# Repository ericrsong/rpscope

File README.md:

This is a clone from jgpeiro's design: https://hackaday.io/project/188051-rpscope/details

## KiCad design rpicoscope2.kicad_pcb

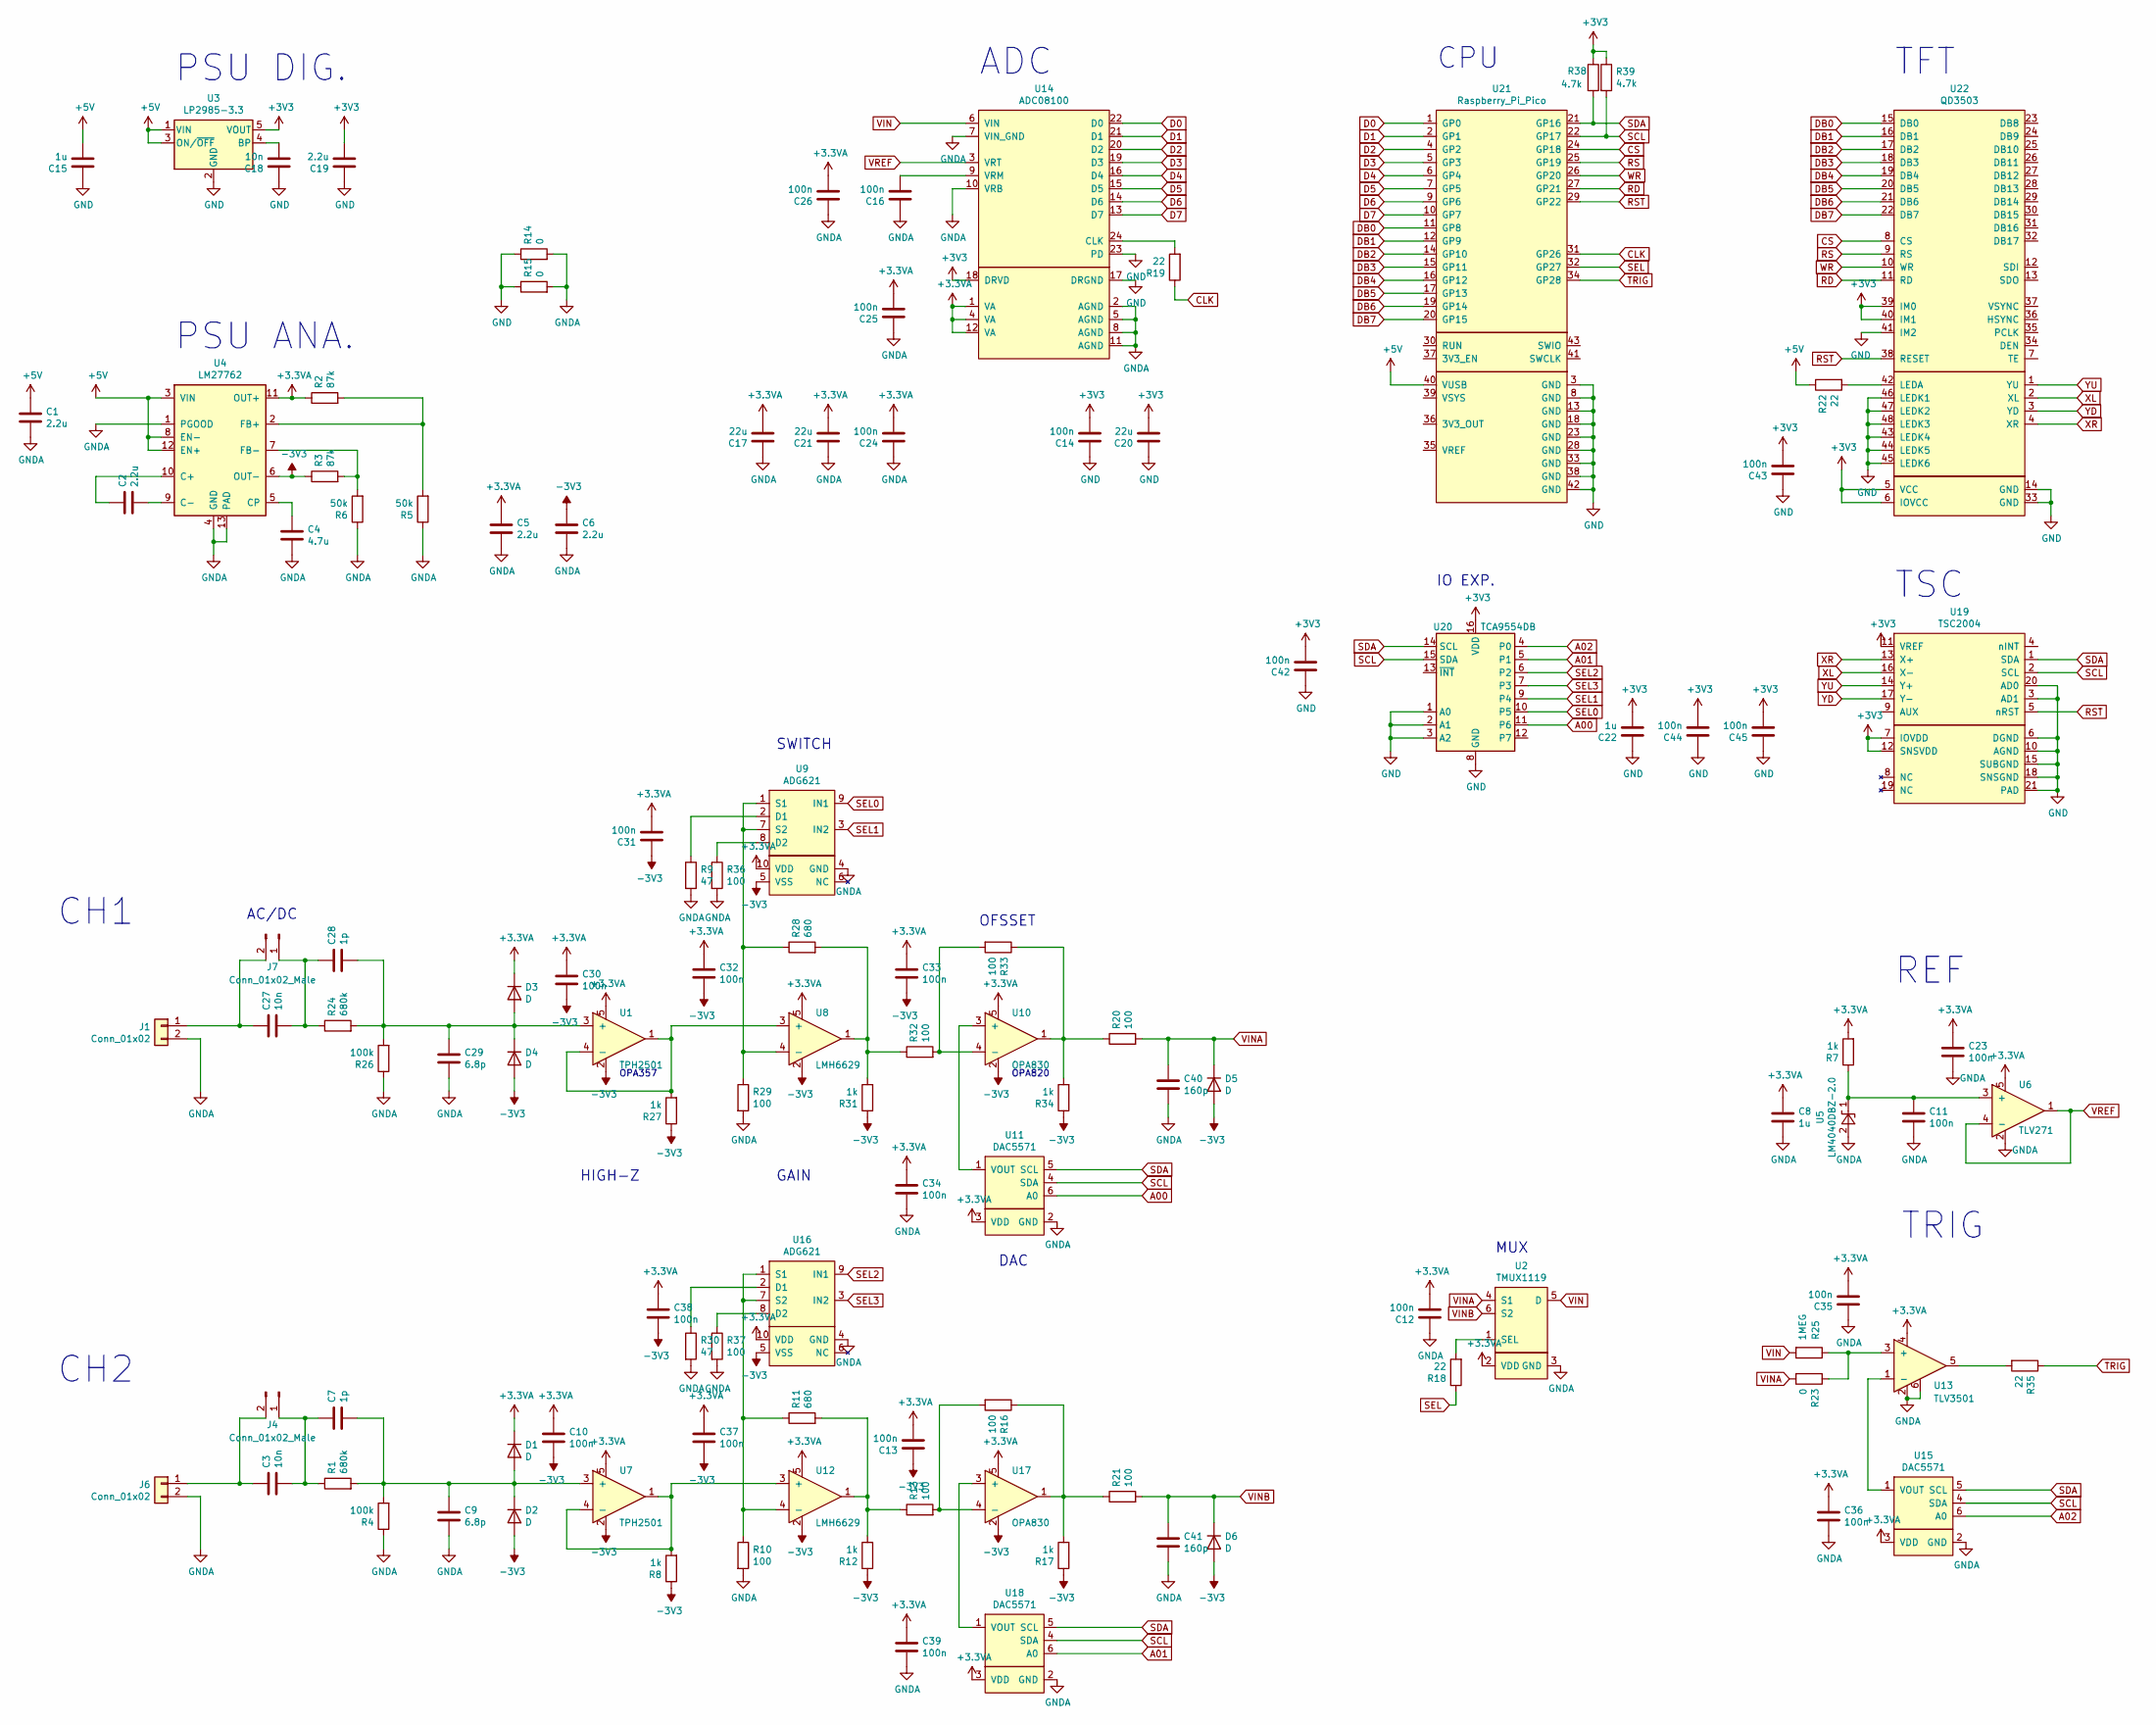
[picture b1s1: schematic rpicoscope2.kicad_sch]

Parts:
C1, C2, C5, C6, C19: 2.2u; C_0603_1608Metric; MFR. Part # CL10A225KO8NNNC; LCSC Part # C23630
C3, C18, C27: 10n; C_0603_1608Metric; MFR. Part # 0603B103K500NT; LCSC Part # C57112
C4: 4.7u; C_0603_1608Metric; MFR. Part # CL10A475KO8NNNC; LCSC Part # C19666
C7, C28: 1p; C_0603_1608Metric; MFR. Part # CL10C010CB8NNNC; LCSC Part # C23969
C8, C15, C22: 1u; C_0603_1608Metric; MFR. Part # CL10A105KB8NNNC; LCSC Part # C15849
C9, C29: 6.8p; C_0603_1608Metric; MFR. Part # 0603CG6R8C500NT; LCSC Part # C1679
C10, C11, C12, C13, C14, C16, C23, C24, C25, C26, C30, C31, C32, C33, C34, C35, C36, C37, C38, C39, C42, C43, C44, C45: 100n; C_0603_1608Metric; MFR. Part # CC0603KRX7R9BB104; LCSC Part # C14663
C17, C20, C21: 22u; C_0603_1608Metric; MFR. Part # CL10A226MQ8NRNC; LCSC Part # C59461
C40, C41: 160p; C_0603_1608Metric; MFR. Part # FN18X104K160PSG; LCSC Part # C235729
D1, D2, D3, D4, D5, D6: D; D_0603_1608Metric
J1, J6: Conn_01x02; SMA_Samtec_SMA-J-P-X-ST-EM1_EdgeMount
J4, J7: Conn_01x02_Male; PinHeader_1x02_P1.00mm_Vertical_SMD_Pin1Left
R1, R24: 680k; R_0603_1608Metric; MFR. Part # 0603WAF6803T5E; LCSC Part # C25822
R2, R3: 87k; R_0603_1608Metric; MFR. Part # 0603WAF8202T5E; LCSC Part # C23254
R4, R26: 100k; R_0603_1608Metric; MFR. Part # 0603WAF1003T5E; LCSC Part # C25803
R5, R6: 50k; R_0603_1608Metric; MFR. Part # 0603WAF1503T5E; LCSC Part # C22807
R7, R8, R12, R17, R27, R31, R34: 1k; R_0603_1608Metric; MFR. Part # 0603WAF1001T5E; LCSC Part # C21190
R9, R30: 47; R_0603_1608Metric; MFR. Part # 0603WAF470JT5E; LCSC Part # C23182
R10, R13, R16, R20, R21, R29, R32, R33, R36, R37: 100; R_0603_1608Metric; MFR. Part # 0603WAF1000T5E; LCSC Part # C22775
R11, R28: 680; R_0603_1608Metric; MFR. Part # 0603WAF6801T5E; LCSC Part # C23212
R14, R15, R23: 0; R_0603_1608Metric; MFR. Part # 0603WAF0000T5E; LCSC Part # C21189
R18, R19, R22, R35: 22; R_0603_1608Metric; MFR. Part # 0603WAF220JT5E; LCSC Part # C23345
R25: 1MEG; R_0603_1608Metric; MFR. Part # 0603WAF220JT5E; LCSC Part # C23345
R38, R39: 4.7k; R_0603_1608Metric; MFR. Part # 0603WAF4701T5E; LCSC Part # C23162
U1, U7: TPH2501; SOT-23-5; LCSC Part # C139385
U2: TMUX1119; SOT-23-6
U3: LP2985-3.3; SOT-23-5; MFR. Part # LP2985-33DBVR; LCSC Part # C95414
U4: LM27762; WSON-12-1EP_3x2mm_P0.5mm_EP1x2.65_ThermalVias; MFR. Part # LM27762DSSR; LCSC Part # C473398
U5: LM4040DBZ-2.0; SOT-23; MFR. Part # LM4040A20IDBZR; LCSC Part # C127070
U6: TLV271; SOT-23-5; LCSC Part # C181500
U8, U12: LMH6629; SOT-23-5; LCSC Part # C206003
U9, U16: ADG621; MSOP-10_3x3mm_P0.5mm; LCSC Part # C208597
U10, U17: OPA830; SOT-23-5; LCSC Part # C181539
U11, U15, U18: DAC5571; SOT-23-6; LCSC Part # C24061
U13: TLV3501; SOT-23-6; LCSC Part # C193413
U14: ADC08100; TSSOP-24_4.4x7.8mm_P0.65mm; LCSC Part # C701581
U19: TSC2004; QFN-20-1EP_4x4mm_P0.5mm_EP2.7x2.7mm; LCSC Part # C128424
U20: TCA9554DB; SSOP-16_5.3x6.2mm_P0.65mm; LCSC Part # C477924
U21: Raspberry_Pi_Pico; RPi_Pico_SMD_TH
U22: QD3503

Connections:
+3.3VA: C5.1, C8.1, C10.1, C12.2, C13.2, C17.2, C21.2, C23.1, C24.2, C25.2, C26.2, C30.1, C31.2, C32.1, C33.1, C34.1, C35.2, C36.1, C37.1, C38.1, C39.1, D1.1 (K), D3.1 (K), R2.1, R7.2, U1.5, U2.2 (VDD), U4.11 (OUT+), U6.5, U7.5, U8.5, U9.10 (VDD), U10.5, U11.3 (VDD), U12.5, U13.4, U14.1 (VA), U14.4 (VA), U14.12 (VA), U15.3 (VDD), U16.10 (VDD), U17.5, U18.3 (VDD)
+3V3: C14.2, C19.2, C20.2, C22.2, C42.2, C43.2, C44.2, C45.2, R38.1, R39.1, U3.5 (VOUT), U14.18 (DRVD), U19.7 (IOVDD), U19.11 (VREF), U19.12 (SNSVDD), U20.16 (VDD), U22.5 (VCC), U22.6 (IOVCC), U22.39 (IM0), U22.40 (IM1)
+5V: C1.1, C15.2, R22.1, U3.1 (VIN), U3.3 (ON/~OFF), U4.3 (VIN), U4.8 (EN-), U4.12 (EN+), U21.40 (VUSB)
-3V3: C6.1, C10.2, C13.1, C30.2, C31.1, C32.2, C33.2, C37.2, C38.2, D2.2 (A), D4.2 (A), D5.2 (A), D6.2 (A), R3.1, R8.1, R12.1, R17.1, R27.1, R31.1, R34.1, U1.2, U4.6 (OUT-), U7.2, U8.2, U9.5 (VSS), U10.2, U12.2, U16.5 (VSS), U17.2
A00: U11.6 (A0), U20.11 (P6)
A01: U18.6 (A0), U20.5 (P1)
A02: U15.6 (A0), U20.4 (P0)
CLK: R19.1, U21.31 (GP26)
CS: U21.24 (GP18), U22.8 (CS)
D0: U14.22 (D0), U21.1 (GP0)
D1: U14.21 (D1), U21.2 (GP1)
D2: U14.20 (D2), U21.4 (GP2)
D3: U14.19 (D3), U21.5 (GP3)
D4: U14.16 (D4), U21.6 (GP4)
D5: U14.15 (D5), U21.7 (GP5)
D6: U14.14 (D6), U21.9 (GP6)
D7: U14.13 (D7), U21.10 (GP7)
DB0: U21.11 (GP8), U22.15 (DB0)
DB1: U21.12 (GP9), U22.16 (DB1)
DB2: U21.14 (GP10), U22.17 (DB2)
DB3: U21.15 (GP11), U22.18 (DB3)
DB4: U21.16 (GP12), U22.19 (DB4)
DB5: U21.17 (GP13), U22.20 (DB5)
DB6: U21.19 (GP14), U22.21 (DB6)
DB7: U21.20 (GP15), U22.22 (DB7)
GND: C14.1, C15.1, C18.1, C19.1, C20.1, C22.1, C42.1, C43.1, C44.1, C45.1, R14.1, R15.1, U3.2 (GND), U14.17 (DRGND), U14.23 (PD), U19.3 (AD1), U19.6 (DGND), U19.10 (AGND), U19.15 (SUBGND), U19.18 (SNSGND), U19.20 (AD0), U19.21 (PAD), U20.1 (A0), U20.2 (A1), U20.3 (A2), U20.8 (GND), U21.3 (GND), U21.8 (GND), U21.13 (GND), U21.18 (GND), U21.23 (GND), U21.28 (GND), U21.33 (GND), U21.38 (GND), U21.42 (GND), U22.14 (GND), U22.33 (GND), U22.41 (IM2), U22.43 (LEDK4), U22.44 (LEDK5), U22.45 (LEDK6), U22.46 (LEDK1), U22.47 (LEDK2), U22.48 (LEDK3)
GNDA: C1.2, C4.2, C5.2, C6.2, C8.2, C9.2, C11.2, C12.1, C16.1, C17.1, C21.1, C23.2, C24.1, C25.1, C26.1, C29.2, C34.2, C35.1, C36.2, C39.2, C40.2, C41.2, J1.2, J6.2, R4.1, R5.1, R6.1, R9.2, R10.2, R14.2, R15.2, R26.1, R29.2, R30.2, R36.2, R37.2, U2.3 (GND), U4.1 (PGOOD), U4.4 (GND), U4.13 (PAD), U5.2 (A), U6.2, U9.4 (GND), U11.2 (GND), U13.2, U13.6, U14.2 (AGND), U14.5 (AGND), U14.7 (VIN_GND), U14.8 (AGND), U14.10 (VRB), U14.11 (AGND), U15.2 (GND), U16.4 (GND), U18.2 (GND)
unnamed: C2.1, U4.10 (C+)
unnamed: C2.2, U4.9 (C-)
unnamed: C3.1, J4.2, J6.1
unnamed: C3.2, C7.1, J4.1, R1.1
unnamed: C4.1, U4.5 (CP)
unnamed: C7.2, C9.1, D1.2 (A), D2.1 (K), R1.2, R4.2, U7.3 (+)
unnamed: C11.1, R7.1, U5.1 (K), U6.3 (+)
unnamed: C16.2, U14.9 (VRM)
unnamed: C18.2, U3.4 (BP)
unnamed: C27.1, J1.1, J7.2
unnamed: C27.2, C28.1, J7.1, R24.1
unnamed: C28.2, C29.1, D3.2 (A), D4.1 (K), R24.2, R26.2, U1.3 (+)
unnamed: R2.2, R5.2, U4.2 (FB+)
unnamed: R3.2, R6.2, U4.7 (FB-)
unnamed: R8.2, U7.1, U7.4 (-), U12.3 (+)
unnamed: R9.1, U9.2 (D1)
unnamed: R10.1, R11.1, U12.4 (-), U16.1 (S1), U16.7 (S2)
unnamed: R11.2, R12.2, R13.1, U12.1
unnamed: R13.2, R16.2, U17.4 (-)
unnamed: R16.1, R17.2, R21.1, U17.1
unnamed: R18.2, U2.1 (SEL)
unnamed: R19.2, U14.24 (CLK)
unnamed: R20.1, R33.1, R34.2, U10.1
unnamed: R22.2, U22.42 (LEDA)
unnamed: R23.1, R25.1, U13.3 (+)
unnamed: R27.2, U1.1, U1.4 (-), U8.3 (+)
unnamed: R28.1, R29.1, U8.4 (-), U9.1 (S1), U9.7 (S2)
unnamed: R28.2, R31.2, R32.1, U8.1
unnamed: R30.1, U16.2 (D1)
unnamed: R32.2, R33.2, U10.4 (-)
unnamed: R35.2, U13.5
unnamed: R36.1, U9.8 (D2)
unnamed: R37.1, U16.8 (D2)
unnamed: U10.3 (+), U11.1 (VOUT)
unnamed: U13.1 (-), U15.1 (VOUT)
unnamed: U17.3 (+), U18.1 (VOUT)
RD: U21.27 (GP21), U22.11 (RD)
RS: U21.25 (GP19), U22.9 (RS)
RST: U19.5 (nRST), U21.29 (GP22), U22.38 (RESET)
SCL: R39.2, U11.4 (SDA), U15.4 (SDA), U18.4 (SDA), U19.2 (SCL), U20.15 (SDA), U21.22 (GP17)
SDA: R38.2, U11.5 (SCL), U15.5 (SCL), U18.5 (SCL), U19.1 (SDA), U20.14 (SCL), U21.21 (GP16)
SEL: R18.1, U21.32 (GP27)
SEL0: U9.9 (IN1), U20.10 (P5)
SEL1: U9.3 (IN2), U20.9 (P4)
SEL2: U16.9 (IN1), U20.6 (P2)
SEL3: U16.3 (IN2), U20.7 (P3)
TRIG: R35.1, U21.34 (GP28)
VIN: R25.2, U2.5 (D), U14.6 (VIN)
VINA: C40.1, D5.1 (K), R20.2, R23.2, U2.4 (S1)
VINB: C41.1, D6.1 (K), R21.2, U2.6 (S2)
VREF: U6.1, U6.4 (-), U14.3 (VRT)
WR: U21.26 (GP20), U22.10 (WR)
XL: U19.16 (X-), U22.2 (XL)
XR: U19.13 (X+), U22.4 (XR)
YD: U19.17 (Y-), U22.3 (YD)
YU: U19.14 (Y+), U22.1 (YU)

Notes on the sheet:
GAIN
CH1
OFSSET
DAC
REF
CH2
PSU ANA.
TFT
TRIG
MUX
PSU DIG.
OPA357
TSC
ADC
OPA820
HIGH-Z
SWITCH
IO EXP.
AC/DC
CPU

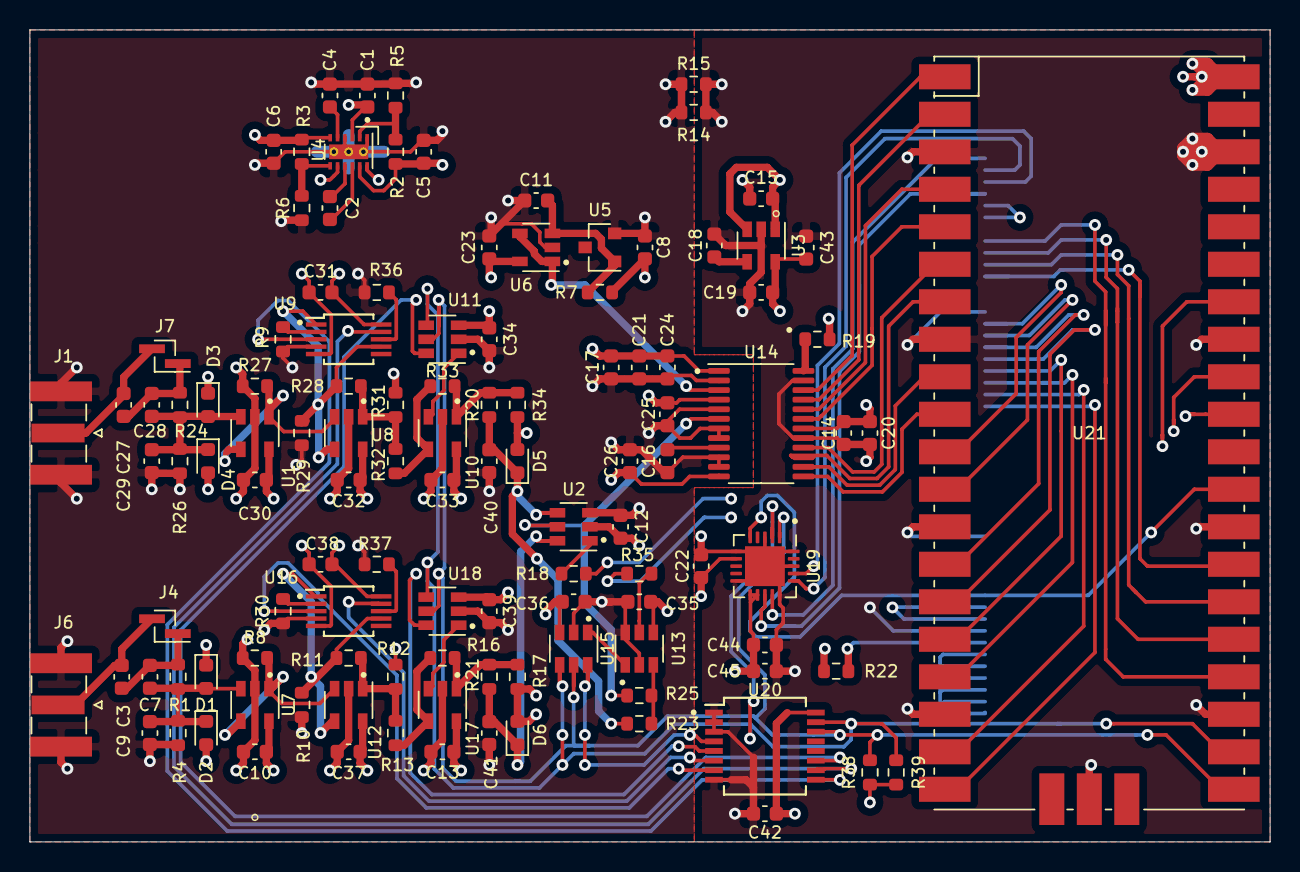
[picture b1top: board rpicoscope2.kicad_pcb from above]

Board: 4 copper layers, 84.0 x 55.0 mm, 116 parts (1 on the bottom side), 83 nets.

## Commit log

2022-11-11 init
2022-11-11 added README
